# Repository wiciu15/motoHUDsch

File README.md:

# motoHUDsch
KiCad Schematic and PCB for STM32F103-based motorcycle digital instrument cluster with 2.8in ILI9341 LCD and X27.168 stepper motor for dial gauge indicator.

<b>Firmware - https://github.com/wiciu15/motoHUDini</b>

<b>Enclosure - https://github.com/wiciu15/motoHUDencl </b>

<b>Demo video - https://youtu.be/awKXkiaZZUE</b>

Rev1 has problems with thermals on 5V regulator, ADC accuracy and other brain farts like bad footprint or silkscreen marking

Rev2 comes with fixes and some new features like button switches. It is not perfect however :/

<b>Rev2 need some mods to work properly:</b>

<b>-U2 needs to be powered from a 5V rail or changed to a rail-to-rail dual opAmp in same package (LM2903 is not rail-to-rail unfortunately)</b>

<b>-C25 and C21 need a parallel resistor to discharge them (100k-200k ohm range)</b>

<b>-startup current is too high and destroys fuses immidately - I switched F1 fuse with a 1206 2,2ohm resistor </b>

If you don't have/like KiCAD there are schematic PDFs and gerber files.

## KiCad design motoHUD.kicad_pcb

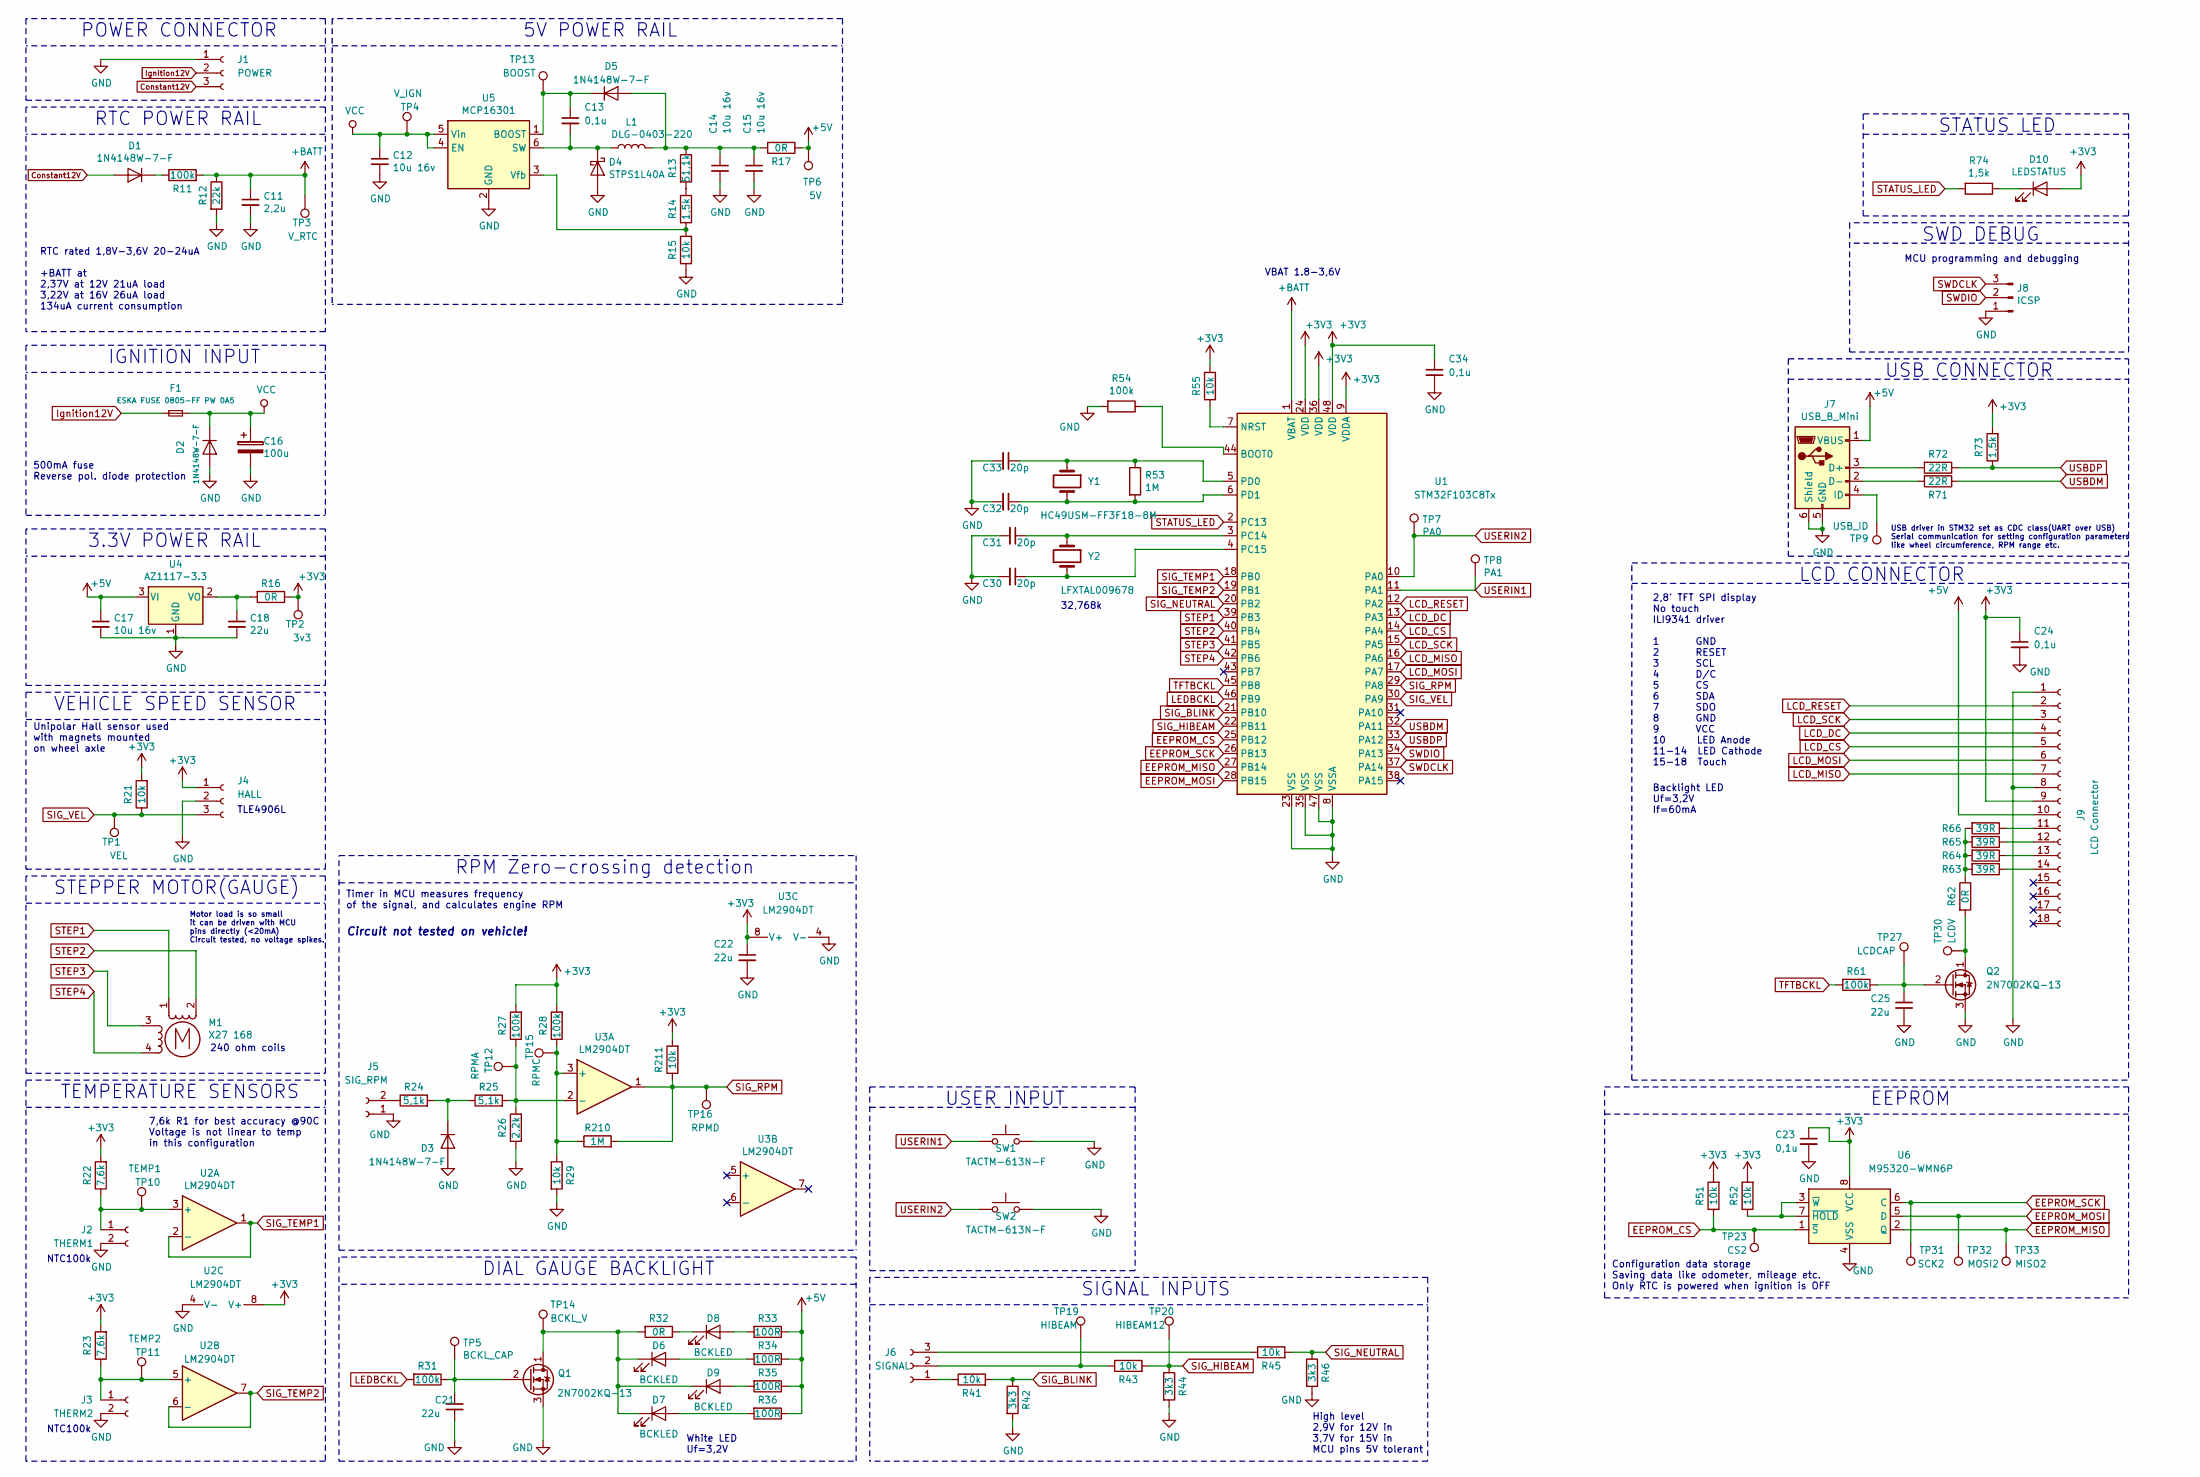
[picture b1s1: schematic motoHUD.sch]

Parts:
C11: 2,2u; C_0805_2012Metric_Pad1.15x1.40mm_HandSolder
C12, C14, C15, C17: 10u 16v; C_0805_2012Metric_Pad1.15x1.40mm_HandSolder
C13, C23, C24, C34: 0,1u; C_0805_2012Metric_Pad1.15x1.40mm_HandSolder
C16: 100u; CP_Radial_D8.0mm_P3.50mm
C18, C21, C22, C25: 22u; C_0805_2012Metric_Pad1.15x1.40mm_HandSolder
C30, C31, C32, C33: 20p; C_0805_2012Metric_Pad1.15x1.40mm_HandSolder
D1, D2, D3, D5: 1N4148W-7-F; D_SOD-123
D4: STPS1L40A; D_SMA_Handsoldering
D6, D7, D8, D9: BCKLED; LED_1206_3216Metric
D10: LEDSTATUS; LED_1206_3216Metric_Pad1.42x1.75mm_HandSolder
F1: ESKA FUSE 0805-FF PW 0A5; C_1206_3216Metric_Pad1.42x1.75mm_HandSolder
J1: POWER; JST_XH_B03B-XH-A_1x03_P2.50mm_Vertical
J2: THERM1; JST_XH_B02B-XH-A_1x02_P2.50mm_Vertical
J3: THERM2; JST_XH_B02B-XH-A_1x02_P2.50mm_Vertical
J4: HALL; JST_XH_B03B-XH-A_1x03_P2.50mm_Vertical
J5: SIG_RPM; JST_XH_B02B-XH-A_1x02_P2.50mm_Vertical
J6: SIGNAL; JST_XH_B03B-XH-A_1x03_P2.50mm_Vertical
J7: USB_B_Mini; USB_Mini-B_Lumberg_2486_01_Horizontal
J8: ICSP; PinHeader_1x03_P2.54mm_Vertical
J9: LCD Connector; ILI9341FFC
L1: DLG-0403-220
M1: X27 168; X27-168
Q1, Q2: 2N7002KQ-13; SOT-23
R11, R27, R28, R31, R54, R61: 100k; R_0805_2012Metric_Pad1.15x1.40mm_HandSolder
R12: 22k; R_0805_2012Metric_Pad1.15x1.40mm_HandSolder
R13: 51,1k; R_0805_2012Metric_Pad1.15x1.40mm_HandSolder
R14, R73, R74: 1,5k; R_0805_2012Metric_Pad1.15x1.40mm_HandSolder
R15, R21, R29, R41, R43, R45, R51, R52, R55, R211: 10k; R_0805_2012Metric_Pad1.15x1.40mm_HandSolder
R16, R17, R32, R62: 0R; R_0805_2012Metric_Pad1.15x1.40mm_HandSolder
R22, R23: 7,6k; R_0805_2012Metric_Pad1.15x1.40mm_HandSolder
R24, R25: 5,1k; R_0805_2012Metric_Pad1.15x1.40mm_HandSolder
R26: 2,2k; R_0805_2012Metric_Pad1.15x1.40mm_HandSolder
R33, R34, R35, R36: 100R; R_0805_2012Metric_Pad1.15x1.40mm_HandSolder
R42, R44, R46: 3k3; R_0805_2012Metric_Pad1.15x1.40mm_HandSolder
R53, R210: 1M; R_0805_2012Metric_Pad1.15x1.40mm_HandSolder
R63, R64, R65, R66: 39R; R_0805_2012Metric_Pad1.15x1.40mm_HandSolder
R71, R72: 22R; R_0805_2012Metric_Pad1.15x1.40mm_HandSolder
SW1, SW2: TACTM-613N-F
TP1: VEL; TestPoint_THTPad_D2.0mm_Drill1.0mm
TP2: 3v3; TestPoint_THTPad_D2.0mm_Drill1.0mm
TP3: V_RTC; TestPoint_THTPad_D2.0mm_Drill1.0mm
TP4: V_IGN; TestPoint_THTPad_D2.0mm_Drill1.0mm
TP5: BCKL_CAP; TestPoint_THTPad_D2.0mm_Drill1.0mm
TP6: 5V; TestPoint_THTPad_D2.0mm_Drill1.0mm
TP7: PA0; TestPoint_THTPad_D2.0mm_Drill1.0mm
TP8: PA1; TestPoint_THTPad_D2.0mm_Drill1.0mm
TP9: USB_ID; TestPoint_THTPad_D2.0mm_Drill1.0mm
TP10: TEMP1; TestPoint_THTPad_D2.0mm_Drill1.0mm
TP11: TEMP2; TestPoint_THTPad_D2.0mm_Drill1.0mm
TP12: RPMA; TestPoint_THTPad_D2.0mm_Drill1.0mm
TP13: BOOST; TestPoint_THTPad_D2.0mm_Drill1.0mm
TP14: BCKL_V; TestPoint_THTPad_D2.0mm_Drill1.0mm
TP15: RPMC; TestPoint_THTPad_D2.0mm_Drill1.0mm
TP16: RPMD; TestPoint_THTPad_D2.0mm_Drill1.0mm
TP19: HIBEAM; TestPoint_THTPad_D2.0mm_Drill1.0mm
TP20: HIBEAM12; TestPoint_THTPad_D2.0mm_Drill1.0mm
TP23: CS2; TestPoint_THTPad_D2.0mm_Drill1.0mm
TP27: LCDCAP; TestPoint_THTPad_D2.0mm_Drill1.0mm
TP30: LCDV; TestPoint_THTPad_D2.0mm_Drill1.0mm
TP31: SCK2; TestPoint_THTPad_D2.0mm_Drill1.0mm
TP32: MOSI2; TestPoint_THTPad_D2.0mm_Drill1.0mm
TP33: MISO2; TestPoint_THTPad_D2.0mm_Drill1.0mm
U1: STM32F103C8Tx; LQFP-48_7x7mm_P0.5mm
U2, U3: LM2904DT; SO-8_5.3x6.2mm_P1.27mm
U4: AZ1117-3.3; SOT-223
U5: MCP16301; SOT-23-6
U6: M95320-WMN6P; SOIC-8_3.9x4.9mm_P1.27mm
Y1: HC49USM-FF3F18-8M; Crystal_SMD_HC49-SD_HandSoldering
Y2: LFXTAL009678; Crystal_SMD_3215-2Pin_3.2x1.5mm

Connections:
+3V3: C22.1, C23.1, C24.1, C34.1, D10.2 (A), J4.1, J9.9, R16.1, R21.2, R22.2, R23.2, R27.2, R28.2, R51.2, R52.2, R55.2, R73.2, R211.2, TP2.1, U1.9 (VDDA), U1.24 (VDD), U1.36 (VDD), U1.48 (VDD), U2.8 (V+), U3.8 (V+), U6.8 (VCC)
+5V: C17.1, J7.1 (VBUS), J9.10, R17.1, R33.1, R34.1, R35.1, R36.1, TP6.1, U4.3 (VI)
+BATT: C11.1, R11.2, R12.1, TP3.1, U1.1 (VBAT)
Constant12V: D1.2 (A), J1.3
EEPROM_CS: R51.1, TP23.1, U1.25 (PB12), U6.1 (~S)
EEPROM_MISO: TP33.1, U1.27 (PB14), U6.2 (Q)
EEPROM_MOSI: TP32.1, U1.28 (PB15), U6.5 (D)
EEPROM_SCK: TP31.1, U1.26 (PB13), U6.6 (C)
GND: C11.2, C12.2, C14.2, C15.2, C16.2, C17.2, C18.2, C21.2, C22.2, C23.2, C24.2, C25.2, C30.2, C31.2, C32.2, C33.2, C34.2, D2.2 (A), D3.2 (A), D4.2 (A), J1.1, J2.2, J3.2, J4.2, J5.1, J7.5 (GND), J7.6 (Shield), J8.1, J9.1, J9.8, Q1.3 (S), Q2.3 (S), R12.2, R15.2, R26.1, R29.2, R42.2, R44.2, R46.2, R54.2, SW1.2, SW2.2, U1.8 (VSSA), U1.23 (VSS), U1.35 (VSS), U1.47 (VSS), U2.4 (V-), U3.4 (V-), U4.1 (GND), U5.2 (GND), U6.4 (VSS)
Ignition12V: F1.1, J1.2
LCD_CS: J9.5, U1.14 (PA4)
LCD_DC: J9.4, U1.13 (PA3)
LCD_MISO: J9.7, U1.16 (PA6)
LCD_MOSI: J9.6, U1.17 (PA7)
LCD_RESET: J9.2, U1.12 (PA2)
LCD_SCK: J9.3, U1.15 (PA5)
LEDBCKL: R31.2, U1.46 (PB9)
unnamed: C13.1, D5.1 (K), TP13.1, U5.1 (BOOST)
unnamed: C13.2, D4.1 (K), L1.1, U5.6 (SW)
unnamed: C14.1, C15.1, D5.2 (A), L1.2, R13.1, R17.2
unnamed: C18.1, R16.2, U4.2 (VO)
unnamed: C21.1, Q1.2 (G), R31.1, TP5.1
unnamed: C25.1, Q2.2 (G), R61.1, TP27.1
unnamed: C30.1, U1.4 (PC15), Y2.2
unnamed: C31.1, U1.3 (PC14), Y2.1
unnamed: C32.1, R53.2, U1.6 (PD1), Y1.2
unnamed: C33.1, R53.1, U1.5 (PD0), Y1.1
unnamed: D1.1 (K), R11.1
unnamed: D3.1 (K), R24.2, R25.1
unnamed: D6.1 (K), D7.1 (K), D9.1 (K), Q1.1 (D), R32.2, TP14.1
unnamed: D6.2 (A), R34.2
unnamed: D7.2 (A), R36.2
unnamed: D8.1 (K), R32.1
unnamed: D8.2 (A), R33.2
unnamed: D9.2 (A), R35.2
unnamed: D10.1 (K), R74.1
unnamed: J2.1, R22.1, TP10.1, U2.3 (+)
unnamed: J3.1, R23.1, TP11.1, U2.5 (+)
unnamed: J5.2, R24.1
unnamed: J6.1, R41.1
unnamed: J6.2, R43.1, TP19.1
unnamed: J6.3, R45.1
unnamed: J7.2 (D-), R71.2
unnamed: J7.3 (D+), R72.2
unnamed: J7.4 (ID), TP9.1
unnamed: J9.11, R66.1
unnamed: J9.12, R65.1
unnamed: J9.13, R64.1
unnamed: J9.14, R63.1
unnamed: Q2.1 (D), R62.2, TP30.1
unnamed: R13.2, R14.1
unnamed: R14.2, R15.1, U5.3 (Vfb)
unnamed: R25.2, R26.2, R27.1, TP12.1, U3.2 (-)
unnamed: R52.1, U6.3 (~W), U6.7 (~HOLD)
unnamed: R54.1, U1.44 (BOOT0)
unnamed: R55.1, U1.7 (NRST)
unnamed: R62.1, R63.2, R64.2, R65.2, R66.2
unnamed: R28.1, R29.1, R210.1, TP15.1, U3.3 (+)
SIG_BLINK: R41.2, R42.1, U1.21 (PB10)
SIG_HIBEAM: R43.2, R44.1, TP20.1, U1.22 (PB11)
SIG_NEUTRAL: R45.2, R46.1, U1.20 (PB2)
SIG_RPM: R210.2, R211.1, TP16.1, U1.29 (PA8), U3.1
SIG_TEMP1: U1.18 (PB0), U2.1, U2.2 (-)
SIG_TEMP2: U1.19 (PB1), U2.6 (-), U2.7
SIG_VEL: J4.3, R21.1, TP1.1, U1.30 (PA9)
STATUS_LED: R74.2, U1.2 (PC13)
STEP1: M1.1, U1.39 (PB3)
STEP2: M1.2 (-), U1.40 (PB4)
STEP3: M1.3, U1.41 (PB5)
STEP4: M1.4, U1.42 (PB6)
SWDCLK: J8.3, U1.37 (PA14)
SWDIO: J8.2, U1.34 (PA13)
TFTBCKL: R61.2, U1.45 (PB8)
USBDM: R71.1, U1.32 (PA11)
USBDP: R72.1, R73.1, U1.33 (PA12)
USERIN1: SW1.1, TP8.1, U1.11 (PA1)
USERIN2: SW2.1, TP7.1, U1.10 (PA0)
VCC: C12.1, C16.1, D2.1 (K), F1.2, TP4.1, U5.4 (EN), U5.5 (Vin)

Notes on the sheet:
2,8' TFT SPI display No touch ILI9341 driver 1 GND 2 RESET 3 SCL 4 D/C 5 CS 6 SDA 7 SDO 8 GND 9 VCC 10 LED Anode 11-14 LED Cathode 15-18 Touch
TLE4906L
NTC100k
EEPROM
LCD CONNECTOR
USB CONNECTOR
SWD DEBUG
STATUS LED
VEHICLE SPEED SENSOR
TEMPERATURE SENSORS
240 ohm coils
STEPPER MOTOR(GAUGE)
DIAL GAUGE BACKLIGHT
White LED Uf=3,2V
Backlight LED Uf=3,2V If=60mA
High level 2,9V for 12V in 3,7V for 15V in MCU pins 5V tolerant
SIGNAL INPUTS
3.3V POWER RAIL
5V POWER RAIL
VBAT 1.8-3,6V
RTC rated 1,8V-3,6V 20-24uA +BATT at 2,37V at 12V 21uA load 3,22V at 16V 26uA load 134uA current consumption
RTC POWER RAIL
IGNITION INPUT
RPM Zero-crossing detection
Configuration data storage Saving data like odometer, mileage etc. Only RTC is powered when ignition is OFF
USB driver in STM32 set as CDC class(UART over USB) Serial communication for setting configuration parameters like wheel circumference, RPM range etc.
MCU programming and debugging
500mA fuse Reverse pol. diode protection
Unipolar Hall sensor used with magnets mounted on wheel axle
Motor load is so small it can be driven with MCU pins directly (<20mA) Circuit tested, no voltage spikes.
Circuit not tested on vehicle!
POWER CONNECTOR
Timer in MCU measures frequency of the signal, and calculates engine RPM
32,768k
7,6k R1 for best accuracy @90C Voltage is not linear to temp in this configuration
USER INPUT

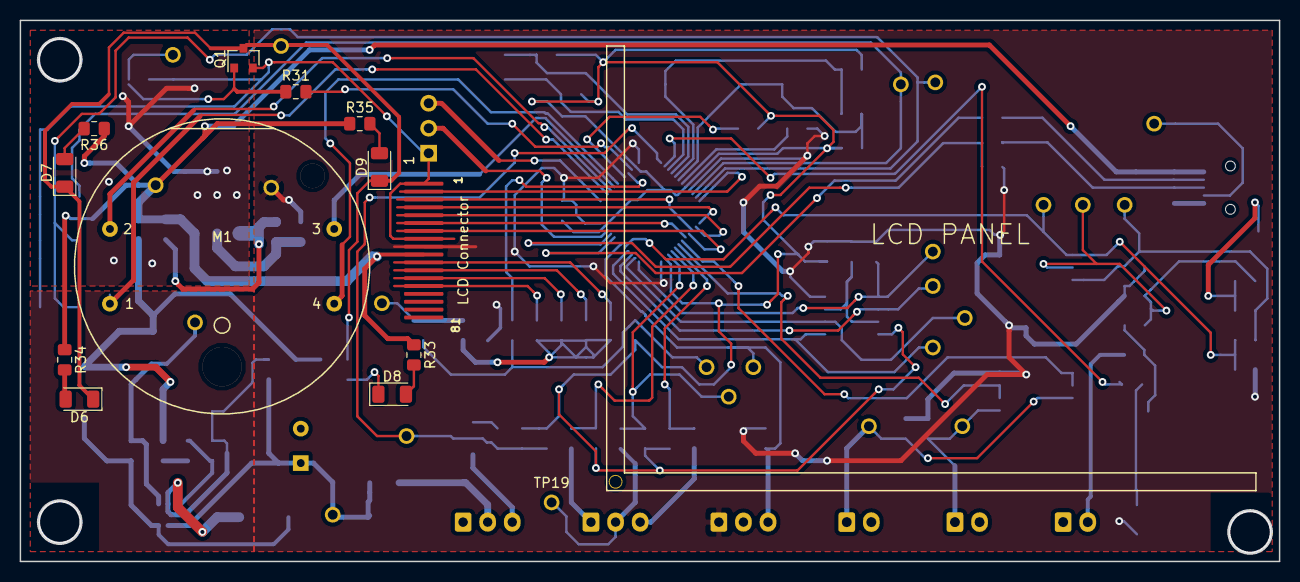
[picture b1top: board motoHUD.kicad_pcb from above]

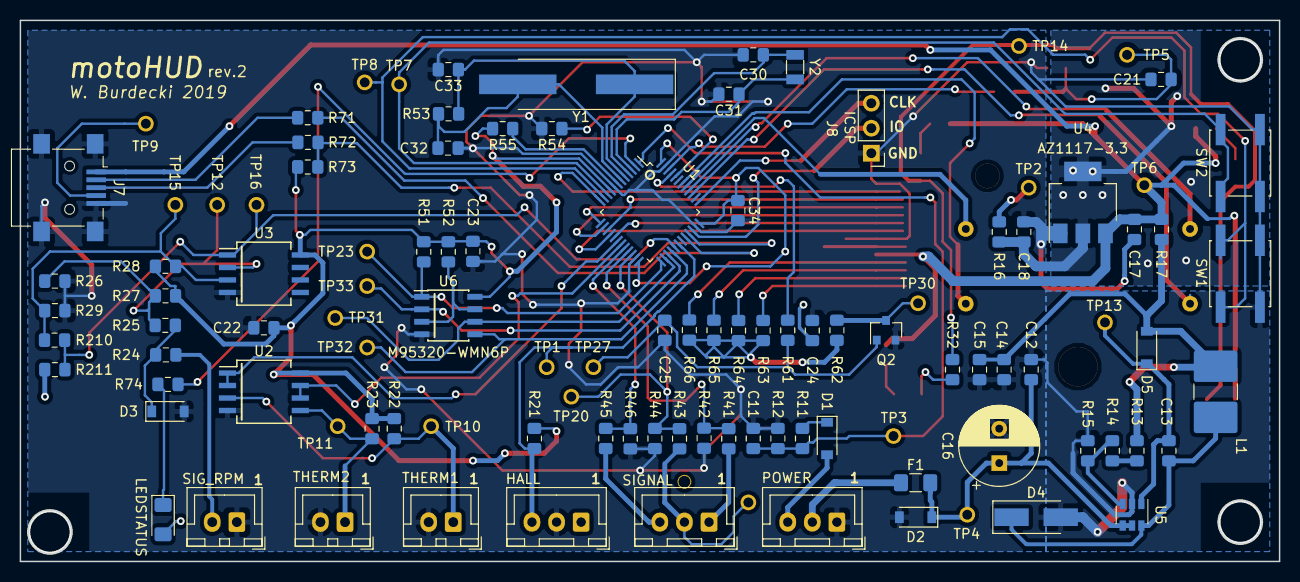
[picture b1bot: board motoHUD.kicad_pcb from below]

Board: 2 copper layers, 128.0 x 55.0 mm, 121 parts (108 on the bottom side), 78 nets.

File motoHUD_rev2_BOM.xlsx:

Item | Qty | Reference(s) | Value | LibPart | Footprint | Link | Cena/szt | Cena
1 | 1 | C11 | 2,2u | Device:C_Small | Capacitor_SMD:C_0805_2012Metric_Pad1.15x1.40mm_HandSolder | ~
2 | 4 | C12, C14, C15, C17 | 10u 16v | Device:C_Small | Capacitor_SMD:C_0805_2012Metric_Pad1.15x1.40mm_HandSolder | ~
3 | 4 | C13, C23, C24, C34 | 0,1u | Device:C_Small | Capacitor_SMD:C_0805_2012Metric_Pad1.15x1.40mm_HandSolder | ~
4 | 1 | C16 | 100u | Device:CP | Capacitor_THT:CP_Radial_D8.0mm_P3.50mm | ~
5 | 4 | C18, C21, C22, C25 | 22u | Device:C_Small | Capacitor_SMD:C_0805_2012Metric_Pad1.15x1.40mm_HandSolder | ~
6 | 4 | C30, C31, C32, C33 | 20p | Device:C_Small | Capacitor_SMD:C_0805_2012Metric_Pad1.15x1.40mm_HandSolder | ~
7 | 4 | D1, D2, D3, D5 | 1N4148W-7-F | Diode:1N4148 | Diode_SMD:D_SOD-123 | https://www.tme.eu/pl/details/1n4148w-7-f/diody-uniwersalne-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
8 | 1 | D4 | STPS1L40A | Diode | Diode_SMD:D_SMA_Handsoldering | https://www.tme.eu/pl/details/stps1l40a/diody-schottky-smd/s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
9 | 4 | D6, D7, D8, D9 | BCKLED | Device:LED | LED_SMD:LED_1206_3216Metric | https://www.tme.eu/pl/details/fyls-1206uwc/diody-led-smd-bia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
10 | 1 | D10 | LEDSTATUS | Device:LED | LED_SMD:LED_1206_3216Metric_Pad1.42x1.75mm_HandSolder | https://www.tme.eu/pl/details/osr51206c1e/diody-led-smd-kolo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
11 | 1 | F1 | ESKA FUSE 0805-FF PW 0A5 | Device:Fuse_Small | Capacitor_SMD:C_1206_3216Metric_Pad1.42x1.75mm_HandSolder | https://www.tme.eu/pl/details/bsmd0805-ss0.5/bezpieczniki-sm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
12 | 1 | J1 | POWER | Connector:Conn_01x03_Female | Connector_JST:JST_XH_B03B-XH-A_1x03_P2.50mm_Vertical | https://www.tme.eu/pl/details/mx-5267-03a/zlacza-sygnalowe-r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
13 | 1 | J2 | THERM1 | Connector:Conn_01x02_Female | Connector_JST:JST_XH_B02B-XH-A_1x02_P2.50mm_Vertical | https://www.tme.eu/pl/details/mx-5267-02a/zlacza-sygnalowe-r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
14 | 1 | J3 | THERM2 | Connector:Conn_01x02_Female | Connector_JST:JST_XH_B02B-XH-A_1x02_P2.50mm_Vertical | https://www.tme.eu/pl/details/mx-5267-02a/zlacza-sygnalowe-r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
15 | 1 | J4 | HALL | Connector:Conn_01x03_Female | Connector_JST:JST_XH_B03B-XH-A_1x03_P2.50mm_Vertical | https://www.tme.eu/pl/details/mx-5267-03a/zlacza-sygnalowe-r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
16 | 1 | J5 | SIG_RPM | Connector:Conn_01x02_Female | Connector_JST:JST_XH_B02B-XH-A_1x02_P2.50mm_Vertical | https://www.tme.eu/pl/details/mx-5267-02a/zlacza-sygnalowe-r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
17 | 1 | J6 | SIGNAL | Connector:Conn_01x03_Female | Connector_JST:JST_XH_B03B-XH-A_1x03_P2.50mm_Vertical | https://www.tme.eu/pl/details/mx-5267-03a/zlacza-sygnalowe-r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
18 | 1 | J7 | USB_B_Mini | Connector:USB_B_Mini | Connector_USB:USB_Mini-B_Lumberg_2486_01_Horizontal | https://www.tme.eu/pl/details/musb-b5-s-ra-smt/zlacza-usb-i-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
19 | 1 | J8 | ICSP | Connector:Conn_01x03_Male | Connector_PinHeader_2.54mm:PinHeader_1x03_P2.54mm_Vertical | goldpin
20 | 1 | J9 | LCD Connector | Connector:Conn_01x18_Female | motoHUD:ILI9341 FFC | https://pl.aliexpress.com/item/32861524235.html?spm=a2g0s.90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
21 | 1 | L1 | DLG-0403-220 | Device:L | Inductor_SMD:L_2816_7142Metric_Pad3.20x4.45mm_HandSolder | https://www.tme.eu/pl/details/dlg-0403-220/dlawiki-smd-mocy/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
22 | 1 | M1 | X27 168 | Motor:Stepper_Motor_bipolar | motoHUD:X27-168 | http://www.infineon.com/dgdl/Application-Note-TLE8110EE_driv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
23 | 2 | Q1, Q2 | 2N7002KQ-13 | Device:Q_NMOS_DGS | motoHUD:SOT-23 | https://www.tme.eu/pl/details/2n7002kq-13/tranzystory-z-kana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
24 | 6 | R11, R27, R28, R31, R54, R61 | 100k | Device:R | Resistor_SMD:R_0805_2012Metric_Pad1.15x1.40mm_HandSolder | ~
25 | 1 | R12 | 22k | Device:R | Resistor_SMD:R_0805_2012Metric_Pad1.15x1.40mm_HandSolder | ~
26 | 1 | R13 | 51,1k | Device:R | Resistor_SMD:R_0805_2012Metric_Pad1.15x1.40mm_HandSolder | ~
27 | 3 | R14, R73, R74 | 1,5k | Device:R | Resistor_SMD:R_0805_2012Metric_Pad1.15x1.40mm_HandSolder | ~
28 | 10 | R15, R21, R29, R41, R43, R45, R51, R52, R55, R211 | 10k | Device:R | Resistor_SMD:R_0805_2012Metric_Pad1.15x1.40mm_HandSolder | ~
29 | 4 | R16, R17, R32, R62 | 0R | Device:R | Resistor_SMD:R_0805_2012Metric_Pad1.15x1.40mm_HandSolder | ~
30 | 2 | R22, R23 | 7,6k | Device:R | Resistor_SMD:R_0805_2012Metric_Pad1.15x1.40mm_HandSolder | ~
31 | 2 | R24, R25 | 5,1k | Device:R | Resistor_SMD:R_0805_2012Metric_Pad1.15x1.40mm_HandSolder | ~
32 | 1 | R26 | 2,2k | Device:R | Resistor_SMD:R_0805_2012Metric_Pad1.15x1.40mm_HandSolder | ~
33 | 4 | R33, R34, R35, R36 | 100R | Device:R | Resistor_SMD:R_0805_2012Metric_Pad1.15x1.40mm_HandSolder | ~
34 | 3 | R42, R44, R46 | 3k3 | Device:R | Resistor_SMD:R_0805_2012Metric_Pad1.15x1.40mm_HandSolder | ~
35 | 2 | R53, R210 | 1M | Device:R | Resistor_SMD:R_0805_2012Metric_Pad1.15x1.40mm_HandSolder | ~
36 | 4 | R63, R64, R65, R66 | 39R | Device:R | Resistor_SMD:R_0805_2012Metric_Pad1.15x1.40mm_HandSolder | ~
37 | 2 | R71, R72 | 22R | Device:R | Resistor_SMD:R_0805_2012Metric_Pad1.15x1.40mm_HandSolder | ~
38 | 1 | SW1 | TACTM-613N-F | Switch:SW_Push | Button_Switch_SMD:SW_SPST_EVQQ2 | https://www.tme.eu/pl/details/tactm-613n-f/mikroprzelaczniki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
39 | 1 | U1 | STM32F103C8Tx | MCU_ST_STM32F1:STM32F103C8Tx | Package_QFP:LQFP-48_7x7mm_P0.5mm | https://www.tme.eu/pl/details/stm32f103c8t6/mikrokontrolery-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
40 | 2 | U2, U3 | LM2904DT | Amplifier_Operational:LM2904 | Package_SO:SO-8_5.3x6.2mm_P1.27mm | https://www.tme.eu/pl/details/lm2904dt/wzmacniacze-operacyjn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
41 | 1 | U4 | AZ1117-3.3 | Regulator_Linear:AZ1117-3.3 | Package_TO_SOT_SMD:SOT-223 | https://www.tme.eu/pl/details/az1117ch-3.3trg1/stabilizatory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
42 | 1 | U5 | MCP16301 | Regulator_Switching:MCP16301 | Package_TO_SOT_SMD:SOT-23-6 | https://www.tme.eu/pl/details/mcp16301t-i_chy/regulatory-nap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
43 | 1 | U6 | M95320-WMN6P | Memory_EEPROM:M95256-WMN6P | Package_SO:SOIC-8_3.9x4.9mm_P1.27mm | https://www.tme.eu/pl/details/m95320-wmn6tp/pamieci-eeprom-s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
44 | 1 | Y1 | HC49USM-FF3F18-8M | Device:Crystal | Crystal:Crystal_SMD_HC49-SD_HandSoldering | https://www.tme.eu/pl/details/hc49usm-ff3f8.00/rezonatory-kw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
45 | 1 | Y2 | LFXTAL009678 | Device:Crystal | Crystal:Crystal_SMD_3215-2Pin_3.2x1.5mm | https://www.tme.eu/pl/details/32.768k-cfpx217/rezonatory-kwa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

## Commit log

2019-07-11 RPM sensing
2019-09-15 Updated PCB layout
2019-10-06 schematic rev2
    2nd revision schematic and updated BOM
2019-10-06 BOM in excel
2019-10-07 new netlist imported to board design
2019-10-07 rev2 layout and footprints updated
    routing TODO
2019-10-10 2nd button switch added and routed PCB
2019-10-13 pcb design improvements
2019-10-21 removed gbr from main dir
